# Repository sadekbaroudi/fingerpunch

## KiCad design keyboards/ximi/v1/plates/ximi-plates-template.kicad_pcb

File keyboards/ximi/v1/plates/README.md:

# ximi fr-4 plates

This includes FR-4 plates to allow you to assemble the ximi pcb with plates, along with the ability to add a modular attachment for the pointing device.

# bom

> **Note**
> This list is only for the case build, but not the entire ximi keyboard build. You'll still need the ximi pcb, trackball sensor pcb, and all the components required for a typical ximi build. See the [ximi product page](https://fingerpunch.xyz/product/ximi/)

To build this style case, you'll need:
* 2 sets of FR-4 plates, found in the fr-4 directory
* 10x - 8mm M2 standoffs
* 20x - 5mm M2 screws + 2 per pointing device
* 2x - M2 4mm heat set inserts per pointing device
* 3D printed attachment per pointing device

# renders

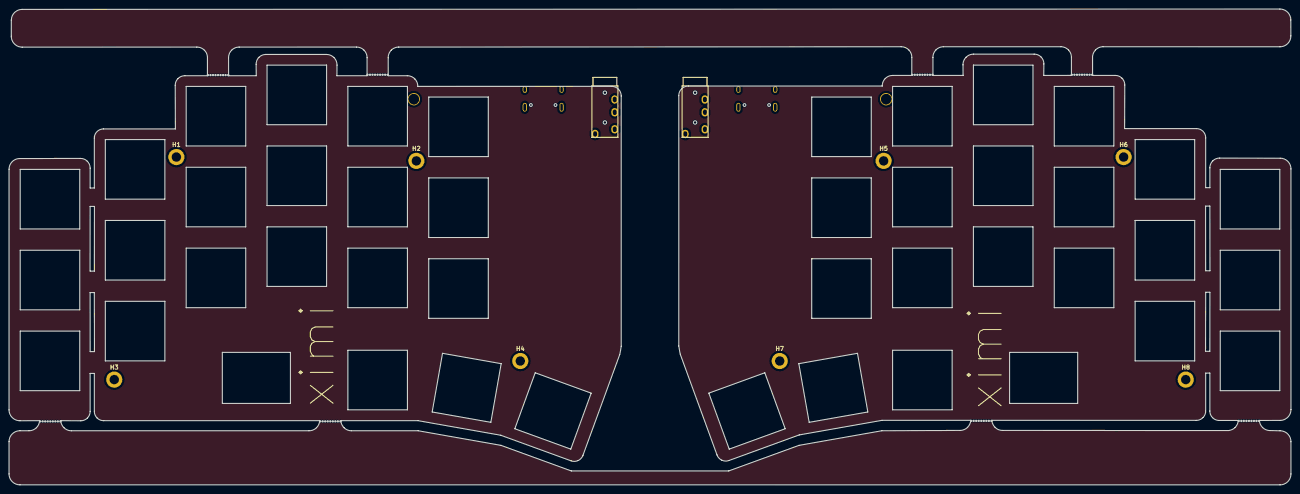
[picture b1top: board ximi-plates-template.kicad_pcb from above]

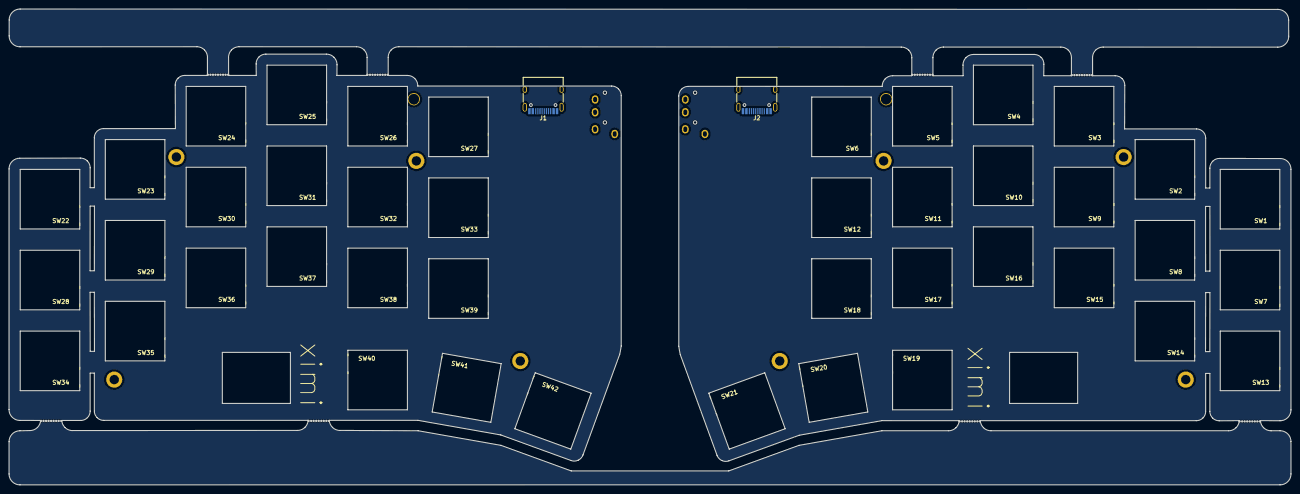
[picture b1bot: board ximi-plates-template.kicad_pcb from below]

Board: 2 copper layers, 301.2 x 111.8 mm, 66 parts (4 on the bottom side), 4 nets, no tracks yet.

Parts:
H1, H2, H3, H4, H5, H6, H7, H8: MountingHole; MountingHole_2.2mm_M2_DIN965_Pad
H9, H10, H11, H12, H13, H14, H15, H16: Breakaway Tabs; Breakaway_Tabs
J1, J2: USB_C_Receptacle_USB2.0; USB_C_Receptacle_HRO_TYPE-C-31-M-12
J7, J11: AudioJack4dpb; TRRS-PJ-320A
SW1, SW2, SW3, SW4, SW5, SW6, SW7, SW8, SW9, SW10, SW11, SW12, SW13, SW14, SW15, SW16, SW17, SW18, SW19, SW20, SW21, SW22, SW23, SW24, SW25, SW26, SW27, SW28, SW29, SW30, SW31, SW32, SW33, SW34, SW35, SW36, SW37, SW38, SW39, SW40, SW41, SW42: SW_Push; switch-cutout-mx
SW47, SW48: RotaryEncoder_Switch; RotaryEncoder_EC11-no-legs
SW49, SW50: SW_Push; MountingHole_2.5mm

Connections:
unnamed: J1.A1 (GND), J1.A12 (GND), J1.B1 (GND), J1.B12 (GND)
unnamed: J1.A4 (VBUS), J1.A9 (VBUS), J1.B4 (VBUS), J1.B9 (VBUS)
unnamed: J2.A1 (GND), J2.A12 (GND), J2.B1 (GND), J2.B12 (GND)
unnamed: J2.A4 (VBUS), J2.A9 (VBUS), J2.B4 (VBUS), J2.B9 (VBUS)

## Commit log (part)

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2022-09-22 trackball build components list
2022-09-22 added notes about the EC11 support
2022-10-01 test modular case for rock on v3 case
2022-10-03 moving firmware into v1 directory so it's clear which to use
2022-10-07 fixed dead link
2022-10-09 added all rock on cases to the fingerpunch repo
2022-10-10 added the rest of the keyboards
2022-10-15 added a new case for an ffkb v1 order, mid profile, low height for integrated atmega, no encoders
2022-10-17 center covers for ffkb v1 case as stls
2022-10-25 more footprints and symbols
2022-10-27 updated branch management
2022-11-08 moved firmware guide to qmk
2022-11-08 added a few new versions of the trackball housing
2022-11-09 added step files for trackball housings with built in BTU
2022-11-27 fixed ffkb v3 trackball cover with tri exposure
2022-11-29 rock on v3.1 rotary encoder center notes
2022-11-30 added a couple of alps footprints
2022-11-30 added trackball case assembly guide
2022-12-07 ffkb oled case and instructions, and new kicad footprints
2022-12-13 led ring low pro case for ffkb
2022-12-13 series of ffkb low pro 5 column oled cases
2022-12-18 chunky low profile case, modeled after the led ring case, but without the opening
2022-12-20 ec-11 encoder knobs
2022-12-23 updated ec11 knobs to have better mounting
2022-12-24 added a new euclid36 case
2022-12-25 added cirque modular attachment for plates
2022-12-26 added simple mx soldered footprint
2022-12-26 rock on svgs
2022-12-31 fixed link to rock on build guide
2023-01-02 more footprints
2023-01-04 adafruit neopixel 5mm bulb and 1x1 THT kicad footprints
2023-01-04 added EC11 versions, and cleaned up the extra opening at the bottom of the case for the ec11 encoder even though it wasn't there
2023-01-05 expanded the cutouts to better fit the controller
2023-01-12 adding ffkb trackball case for low profile switches
2023-01-22 added a prototype footprint that supports ks27, choc v1, and mx hotswap
2023-01-28 made the ffkb v3 encoder fix clearer
2023-02-02 more lowpro chunky cases
2023-02-08 rock on low pro modular and flat cover
2023-02-12 arc reactor emblem for ffkb chunky case series
2023-02-15 added a couple of low profile cases that can be used with a hand soldered usb-c connector
2023-02-18 added a no mount version of the charybdis breakout board
2023-02-22 first attempt at ultra low pro modular case
2023-02-23 v3 high pro choc to v2 cirque adapter
2023-02-23 version of rock on choc v2 modular cover that's better for 3D printing
2023-03-05 added new USB-c footprint that's better for svg exports from kicad
2023-03-06 starting to put together ximi cases for the rp2040 version, now called v1
2023-03-14 added ximi 6 column trackball bottom plates
2023-03-16 added trackball cover with even wider bottom edge, this one works best on my snapmaker A350T
2023-03-18 new footprints and updated neopixel bulb footprint from adafruit
2023-03-20 added stenographobe plates
2023-03-23 tenbit case with cirque holder
2023-03-28 new luakeeb case
2023-03-30 some case updates, euclid36 new case and ffkb lite updates to make it a bit taller
2023-03-30 added dxf for hole cover
2023-04-12 adding some ximi step files so people can modify if they like
2023-04-17 ffkb high pro cirque with evq on left only
2023-04-18 added annotated breakout pins for ximi v1 pcb
2023-04-18 added no pointing device cases for ximi
2023-04-21 added new sideways mounted addressable led, provided by klackygears
2023-04-25 ximi cases, added 5 column no pointing device cases
2023-04-26 added 7 degree tented bottom plate
2023-05-02 added a few more usb-c footprints
2023-05-02 added clearer instructions for which files to use in ximi v1 case
2023-05-04 added images of haptic to the build guide
2023-05-06 tenbit 4x12 choc case
2023-05-08 added svgs for bottom plates for ximi
2023-05-12 added support for waveshare 1.47 inch display, sku 22224, to the ximi thumb trackball cases
2023-05-16 rectangular rock on cases
2023-05-22 added ks27 choc v1 mx hotswap reversible footprint
2023-05-24 added vik logo footprints
2023-05-29 added version with no ring pattern, along with step file
2023-06-01 added spacer for extra height for acrylic bottom plates, as well as 5 column unibody 57mm trackball case
2023-06-03 was missing a cutout on the top side for MX hotswap
2023-06-06 added instructions for fpc cable connection for trackball
2023-06-11 template for ximi plates, to be completed later
2023-06-13 more progress on ximi plates, now have pointing device plates template
2023-06-13 added readme and renders
2023-06-13 made room for the pcb mounting screw in the trackball holder
2023-06-13 added readme with images
2023-06-15 ffkb rp2040 usb-hub 5 column cases and more renders
2023-06-22 added trackball cover for ximi that extends to the edge, which looks nicer
2023-06-25 added 5 way tactile switches symbol and footprint
2023-06-29 fixed hole size for better fit on D shafts, and added a new one with handles
2023-07-01 fixed edge cuts on center cutout
2023-07-03 one more set of footprint updates to help with exporting svgs for 3D modeling
2023-07-07 no longer need the cases directory, as it's moved into the v1 directory
2023-07-11 added choc trackball cases for the ximi
2023-07-12 heat set insert depths were incorrect
2023-07-13 there was a slight notch in the 5 column cirque cases, fixed
2023-07-16 first pass a vulpes majora cases
2023-07-19 vulpes majora - fixed spacing for PER56 scroll ring, expanded 5 way switch hole size, and made indents for 3 way thumb toggle
2023-07-19 updated ximi bottom plates to better fit usb port and 3 way thumb rocker
2023-07-20 same as last commit, but for the cirque cases
2023-07-22 in previous commit for ximi choc cirque cases, heat set insert holes were removed my mistake, adding back in
2023-07-27 more pinkies out v3 center covers, and a printable bottom plate with spacer
2023-07-28 renamed to make spacer height obvious
2023-08-01 vuples majora 52.5mm trackball for unibody case
2023-08-05 added ffkb soldered switch alignment template
2023-08-09 added 2mm thick bottom plate for euclid36
2023-08-10 ximi choc trackball case - a previous commit removed the EC11 cutout, added back in
2023-08-15 added some modular split vulpes majora cases
2023-08-15 added a couple of magnet size variations for vulpes majora split
2023-08-15 fixed overlapping area on vik module stl with vulpes majora split case
2023-08-16 forgot fpc cutouts in vik module on the last commit
2023-08-16 5.5mm stem 5 way switch handles
2023-08-17 expanded vik fpc cutout to make it easier to plug the cable in
2023-09-22 updated paramtetric trackball holder, the sensor cutout extended too far, and caused the bearing holes to be incomplete
2023-10-01 first commit to test new CMY keycaps
2023-10-02 added keys with homing bumps
2023-10-03 added new case and svg for ffkb lite min-y
2023-10-06 added 34mm trackball housing and cover for per56 scroll ring
2023-10-12 added 6.1mm EC11 knobs and added suffix to originals, indicating 6.5mm
2023-10-12 new EC11 knob called mushroom, suggestion by pyntiehet
2023-10-21 fixed MX stems for CMY keycaps
2023-10-21 added 12 degree version of the CMY keycaps, untested
2023-10-21 added a flat ends version of the 12 degree keycaps
2023-10-25 fixed magnet locations for vulpes majora 52.5 trackball cover
2023-10-26 accidentally commited some extra unneeded files
2023-10-27 added support for MX steps for 12 degree keycaps
2023-10-27 small typo in CMY readme
2023-11-02 added heat set insert mounts for vulpes stock vik module
2023-11-06 fixed 5 way nav cutout, and usb pcb cutout in vulpes majora choc trackball cases
2023-11-09 added a couple of kicad footprints for 2mm pitch pads, both regular and castellated
2023-11-10 updated ffkb v4 readme to have correct links and name references
2023-12-05 step file for USB-C for kicad
2023-12-11 added some joystick symbols and footprints
2023-12-11 removing vik footprints since they are now in the vik repo
2023-12-12 ffkb lite curved cirque 6 column case
2023-12-24 added more vik ec11 module covers for ffkb lite
2023-12-25 added dxf for various bottom plate dxf so you can cut a frosted acrylic bottom plate to show off an underglow setup
2023-12-31 ximi with a hole for the trackpoint, and made the height 2mm taller to give room under the PCB for the trackpoint module
2023-12-31 accidentally removed heat set inserts in ximi 6 trackpoint mx case
2024-01-08 added various tenting angles by adjusting the percentage of the legnth that folds
2024-01-10 added filet on the end to make it nicer, made contact points smaller, increased gaps between hinges to print better at smaller sizes
2024-01-21 also added ssbb's trackpoint pcb footprint
2024-01-29 new ffkb v4 rp2040 cases
2024-01-31 ffkb lite wireless bodies and bottom plate, and fingerpunch emblem plug for 35mm cirque hole
2024-02-02 adjusted emblem fitting to closer to 35mm to make a tighter fit
2024-02-11 added a low pro choc pimoroni evq case for ffkb v1 atmega
2024-02-26 experimental labret covers for trackpoint stem
2024-02-29 kucheza 5 way switch needed additional cutout in choc version to make room for switch housing
2024-03-06 R1 keycaps for CMY 5 degree
2024-03-07 ffkb atmega choc 5 col evq pimoroni case
2024-03-13 added 3.5mm 5 way switch knobs
2024-04-08 moved modular plates around, and added svgs for the 5 col ffkb
2024-04-18 Update README.md with video
2024-04-19 including all step and fusion 360 files for trackball thumb helmet
2024-04-19 Add MIT LICENSE
2024-04-22 ffkb oled cover support
2024-04-23 pointing to ximi v1 build guide from v2
2024-04-23 had wrong version, mx was actually choc, swapped name and added real MX version
2024-04-26 explanation about ffkb lite bottom plate selection
2024-05-08 ffkb lite choc wireless case bodies
2024-05-10 ximi v2 per56 case cutout for per56 was a bit too large
2024-05-13 lowered bearing positions plane down by 0.5mm and added filets on bearing cutouts
2024-05-14 lowered bearing mounts by 0.2mm instead of previous lowering by 0.5mm and added filet
2024-05-15 added wing bearings to thumb trackball vik xs for better stability
2024-05-20 ffkb case for v2 high pro and bottom plate with battery space
2024-06-04 uxcell a14092600ux0438 solenoid model and holder
2024-06-14 ili9341 display module housing and cover
2024-06-20 initial case support for ximega
2024-06-21 a lot more ximega cases, wawa weewa
2024-06-21 ximega weact st7735 cover
2024-06-24 new version of parametric trackball housing that lowers the base height
2024-06-27 pinkies out v3 bottom plate to surround choc plates
2024-07-01 ffkb v4 mx 5 column cirque body
2024-07-07 better support for mounting points on pinkies out v3 cases for center module
2024-07-08 pinkies out v3 mx vik cirque
2024-07-09 pinkies out v3 choc vik 24mm trackball and cover
2024-07-15 pinkies out v3 mx trackball options
2024-07-24 combined bottom plates, since they are identical
2024-08-06 pinkies out v3 case for vik xs with 24mm trackball
2024-08-12 ffkb lite min-y 6 column case with 25mm trackball support
2024-08-21 rp2040 and nrf52840 combined controller and symbol
2024-08-24 4x bearing version of trackball housing for ffkb v3
2024-08-27 rock on v2 high pro mx with evq - expanded evq cutouts a bit for better fit
2024-08-31 kucheza byomcu special edition case
2024-09-01 kucheza byomcu case bottom plate cutout for on off switch wasn't long enough
2024-09-30 ffkb v1 atmega low pro with 3 encoder cutouts
2024-10-19 additional step files for ximi unibody 57mm trackball case
2024-11-19 tenbit bootloader with instructions
2025-02-07 rock on v3 mx modular case with 6 degree tent
2025-03-11 rock on v3 low pro mx cases
2025-04-07 ffkb wireless edition v1 cases
2025-04-09 refined ffkb wireless edition cases readme, added mid-bot plates
